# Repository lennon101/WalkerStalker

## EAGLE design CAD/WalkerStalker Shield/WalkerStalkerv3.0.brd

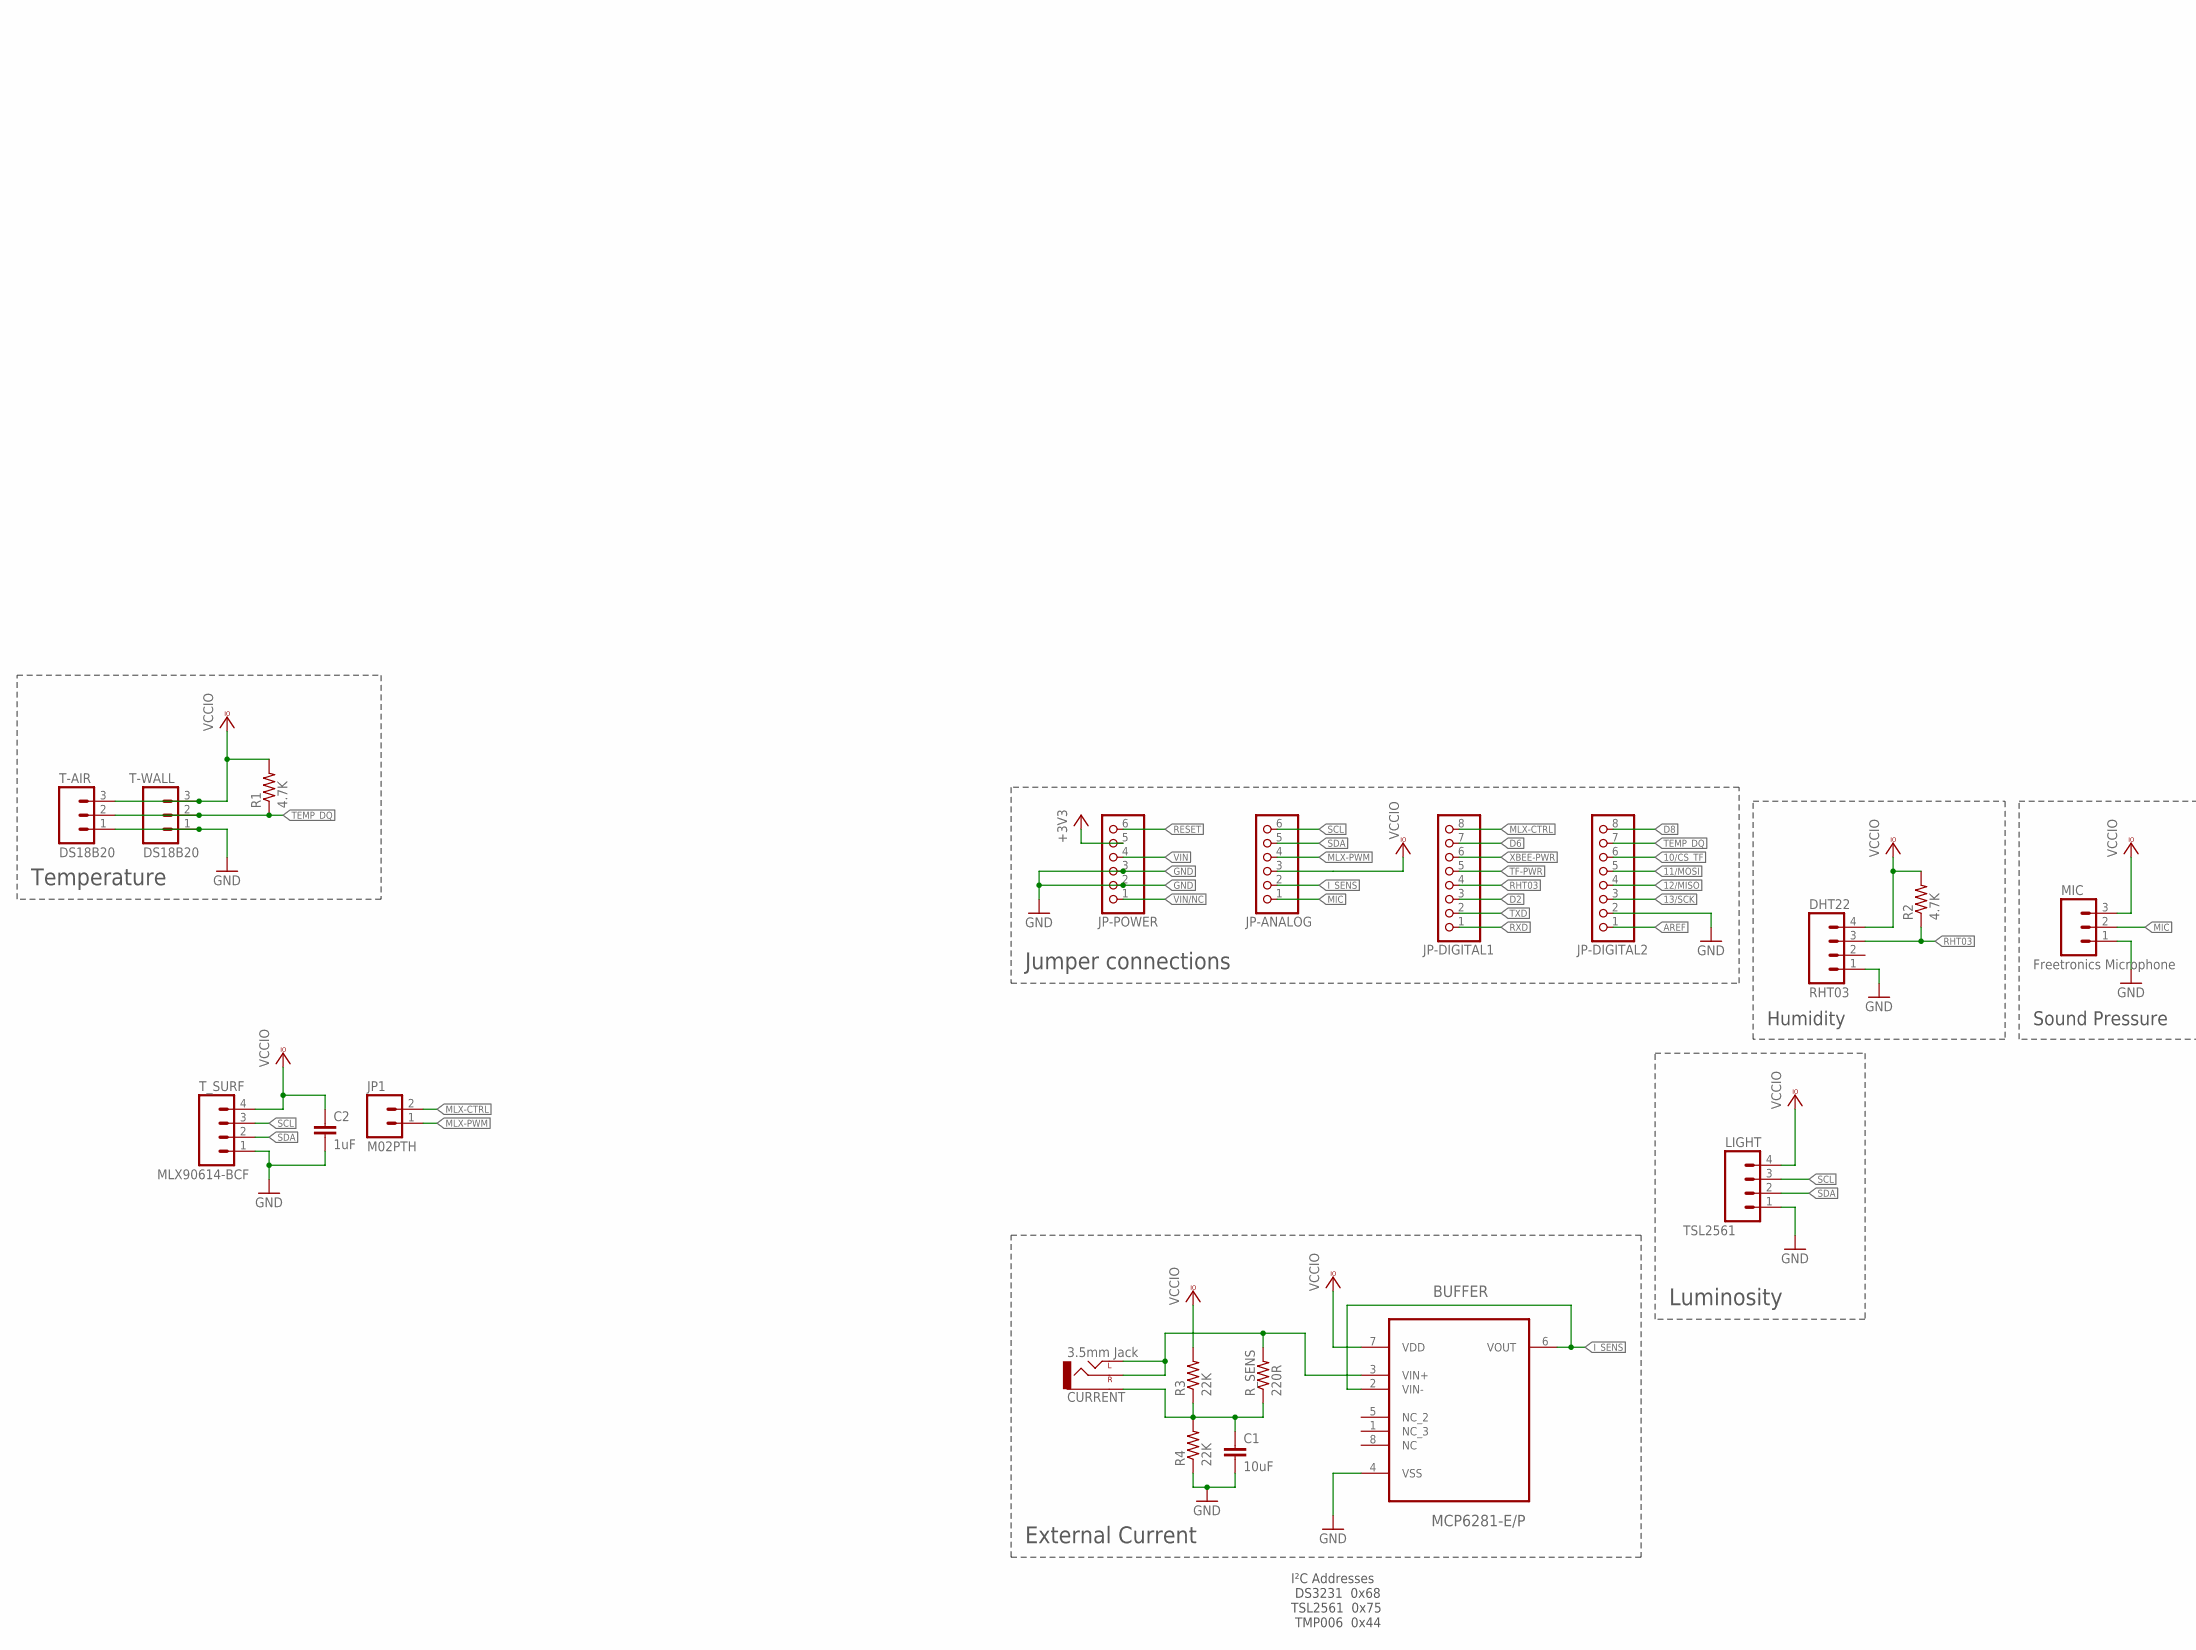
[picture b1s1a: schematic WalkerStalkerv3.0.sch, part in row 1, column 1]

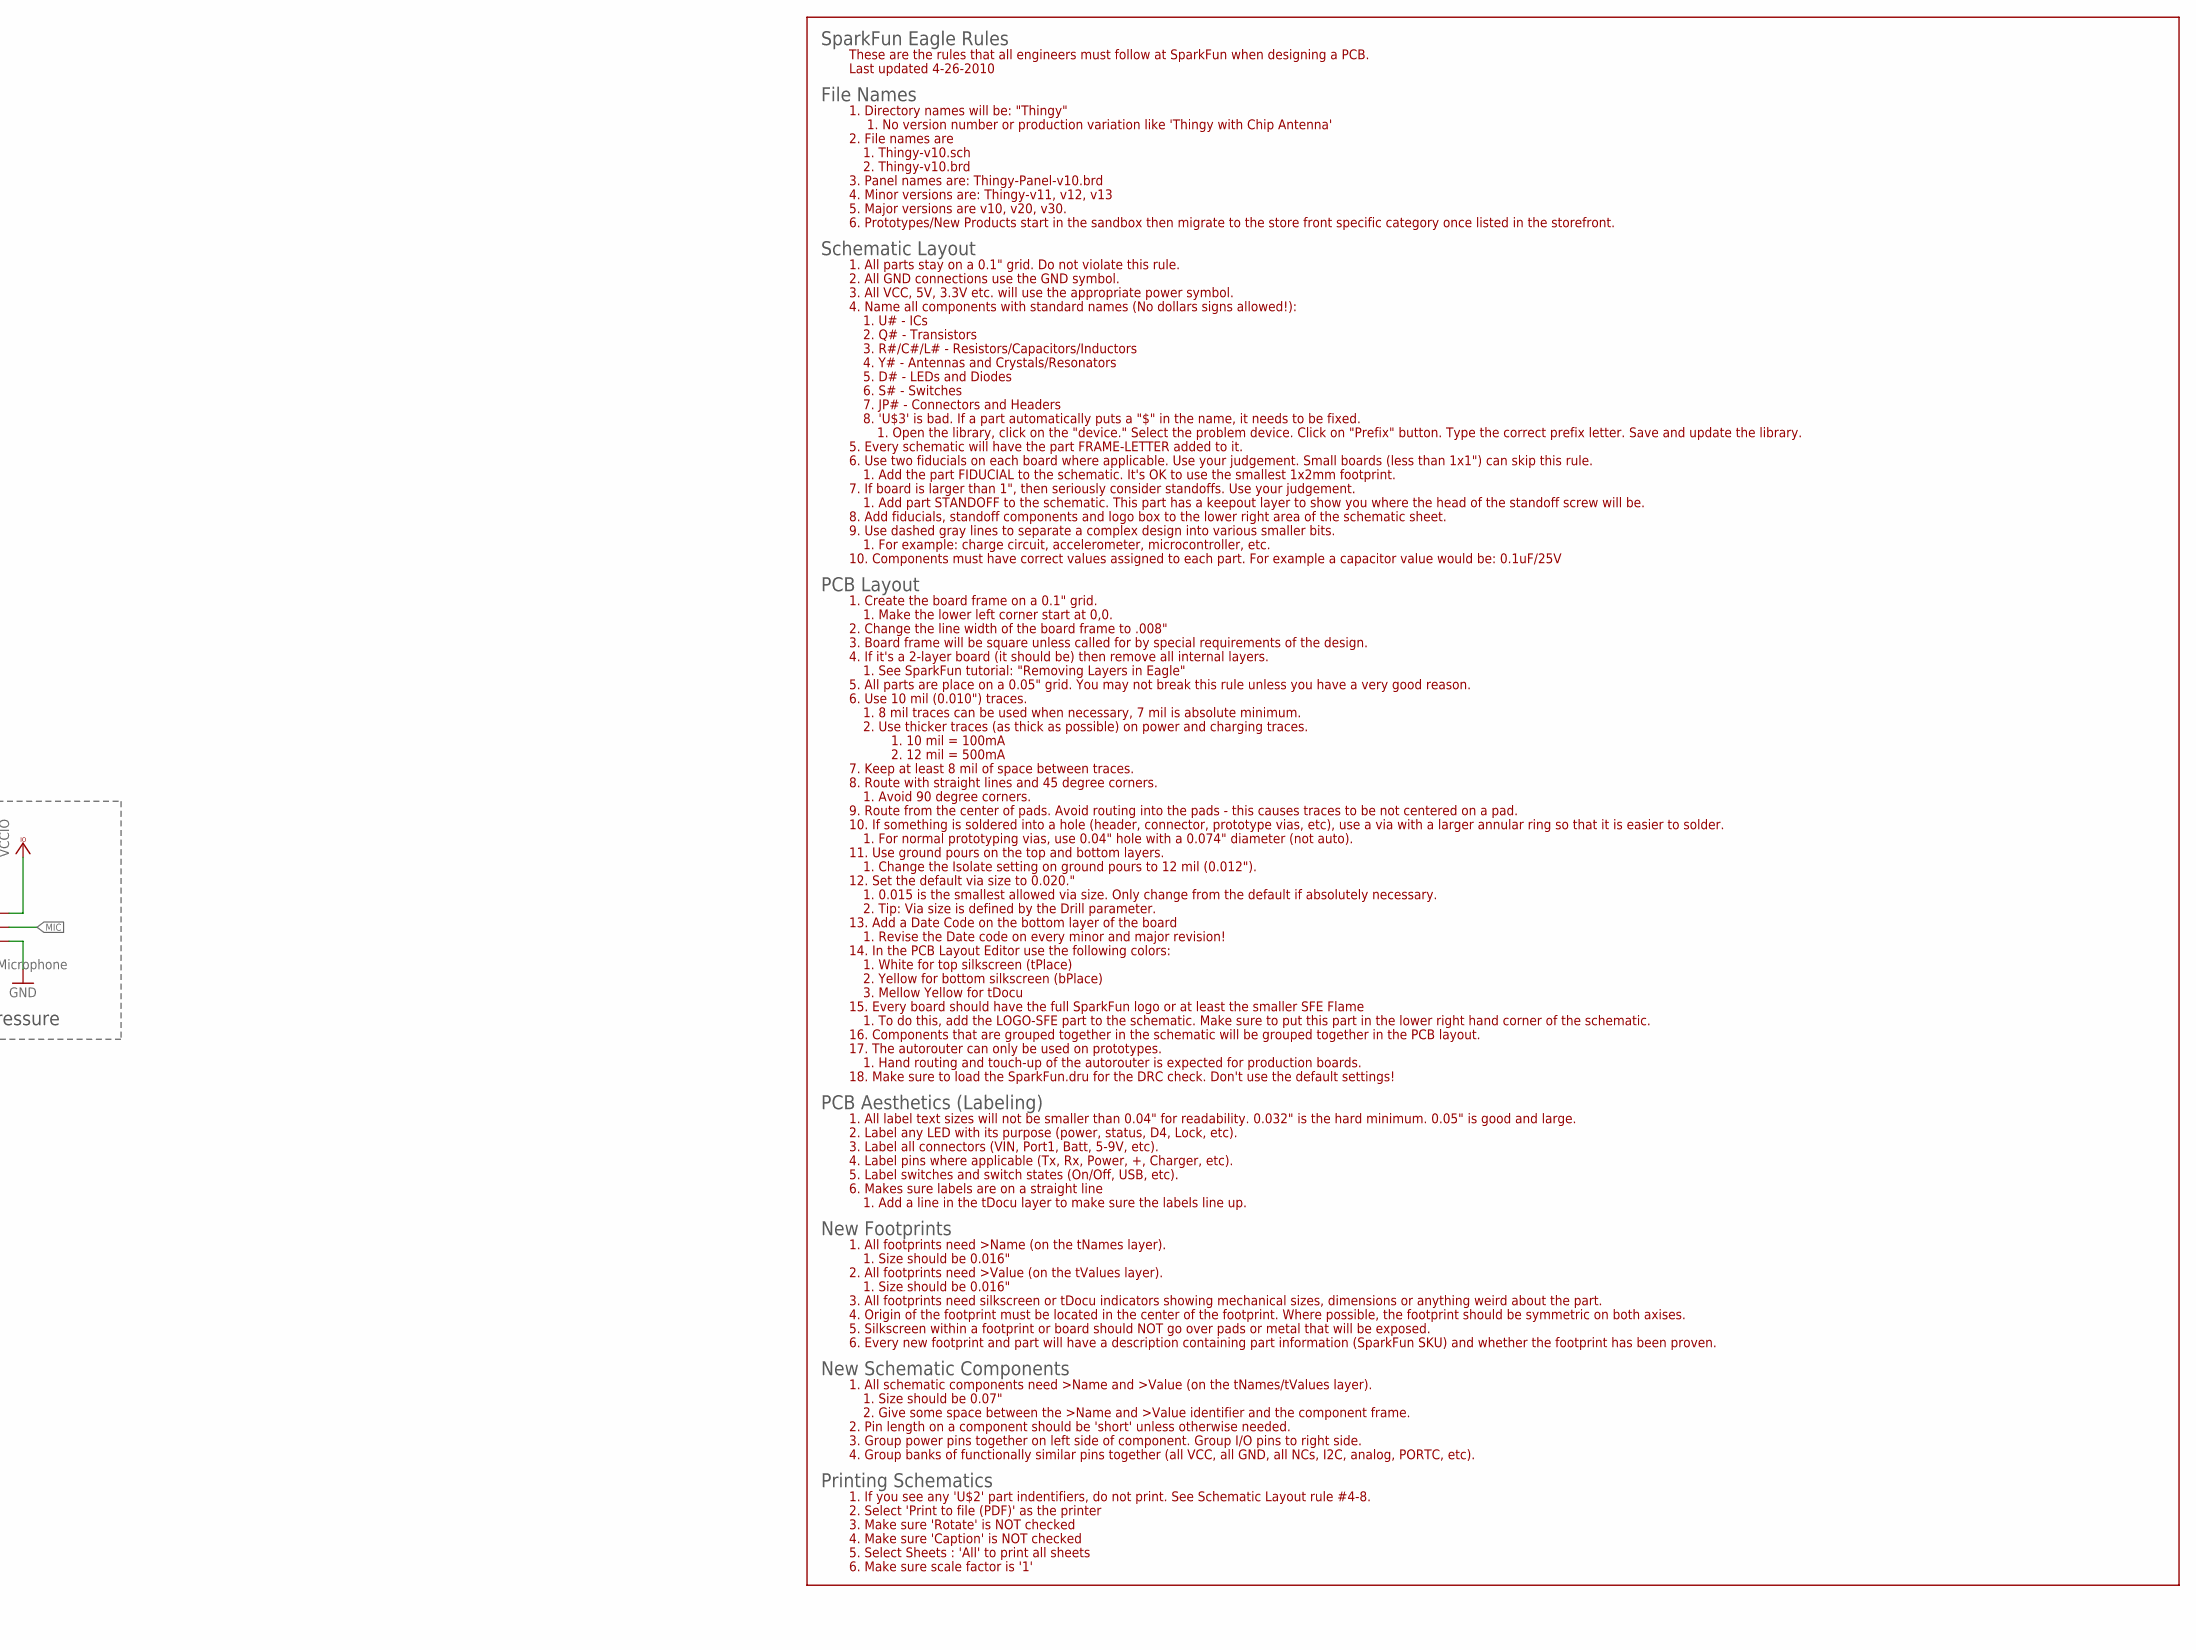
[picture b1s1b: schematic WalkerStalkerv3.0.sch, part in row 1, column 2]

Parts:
BUFFER: MCP6281-E/P; DIP254P762X432-8
C1: 10uF; 1206
C2: 1uF; 1206
CURRENT: 3.5mm Jack; AUDIO-JACK
DHT22: RHT03; 1X04
JP1: M02PTH; 1X02
JP-ANALOG: PINHD-1X6CB; 1X06-CLEANBIG
JP-DIGITAL1, JP-DIGITAL2: PINHD-1X8CLEANBIG; 1X08-CLEANBIG
JP-POWER: PINHD-1X6CB; 1X06-CLEANBIG
LIGHT: TSL2561; 1X04
MIC: Freetronics Microphone; 1X03
R1, R2: 4.7K; 1206
R3, R4: 22K; 1206
R_SENS: 220R; 1206
T-AIR: DS18B20; 1X03
T-WALL: DS18B20; 1X03
T_SURF: MLX90614-BCF; 1X04

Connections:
10/CS_TF: JP-DIGITAL2.6
11/MOSI: JP-DIGITAL2.5
12/MISO: JP-DIGITAL2.4
13/SCK: JP-DIGITAL2.3
+3V3: JP-POWER.5
AREF: JP-DIGITAL2.1
D2: JP-DIGITAL1.3
D6: JP-DIGITAL1.7
D8: JP-DIGITAL2.8
GND: BUFFER.4 (VSS), C1.2, C2.2, DHT22.1, JP-DIGITAL2.2, JP-POWER.2, JP-POWER.3, LIGHT.1, MIC.1, R4.1, T-AIR.1, T-WALL.1, T_SURF.1
I_SENS: BUFFER.2 (VIN-), BUFFER.6 (VOUT), JP-ANALOG.2
MIC: JP-ANALOG.1, MIC.2
MLX-CTRL: JP1.2, JP-DIGITAL1.8
MLX-PWM: JP1.1, JP-ANALOG.4
unnamed: BUFFER.3 (VIN+), CURRENT.RING (RIGHT), CURRENT.TIP (LEFT), R_SENS.2
unnamed: C1.1, CURRENT.SLEEVE, R3.1, R4.2, R_SENS.1
RESET: JP-POWER.6
RHT03: DHT22.3, JP-DIGITAL1.4, R2.1
RXD: JP-DIGITAL1.1
SCL: JP-ANALOG.6, LIGHT.3, T_SURF.3
SDA: JP-ANALOG.5, LIGHT.2, T_SURF.2
TEMP_DQ: JP-DIGITAL2.7, R1.1, T-AIR.2, T-WALL.2
TF-PWR: JP-DIGITAL1.5
TXD: JP-DIGITAL1.2
VCCIO: BUFFER.7 (VDD), C2.1, DHT22.4, JP-ANALOG.3, LIGHT.4, MIC.3, R1.2, R2.2, R3.2, T-AIR.3, T-WALL.3, T_SURF.4
VIN: JP-POWER.4
VIN/NC: JP-POWER.1
XBEE-PWR: JP-DIGITAL1.6

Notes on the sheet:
Jumper connections
External Current
Temperature
Humidity
Luminosity
Sound Pressure
I²C Addresses DS3231 0x68 TSL2561 0x75 TMP006 0x44

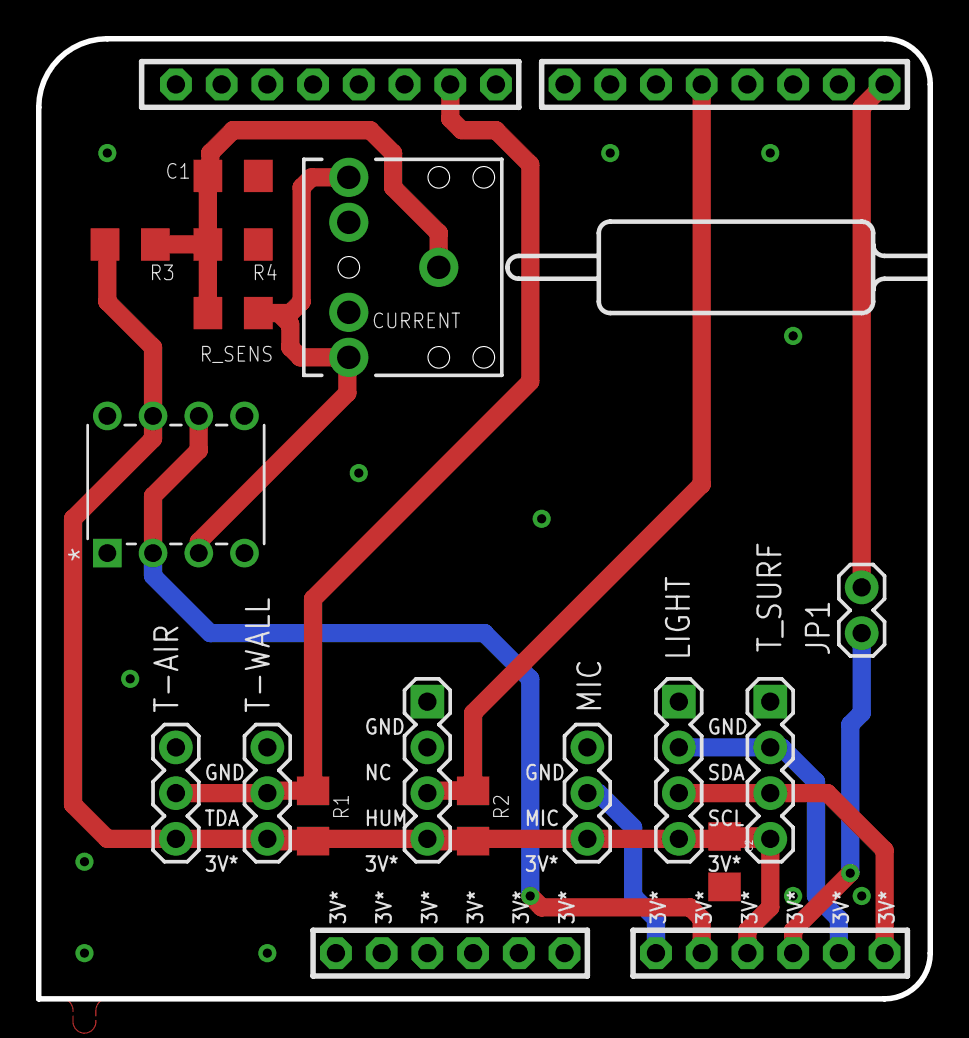
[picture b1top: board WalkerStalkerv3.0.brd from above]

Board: 2 copper layers, 49.5 x 53.3 mm, 20 parts (0 on the bottom side), 12 nets.

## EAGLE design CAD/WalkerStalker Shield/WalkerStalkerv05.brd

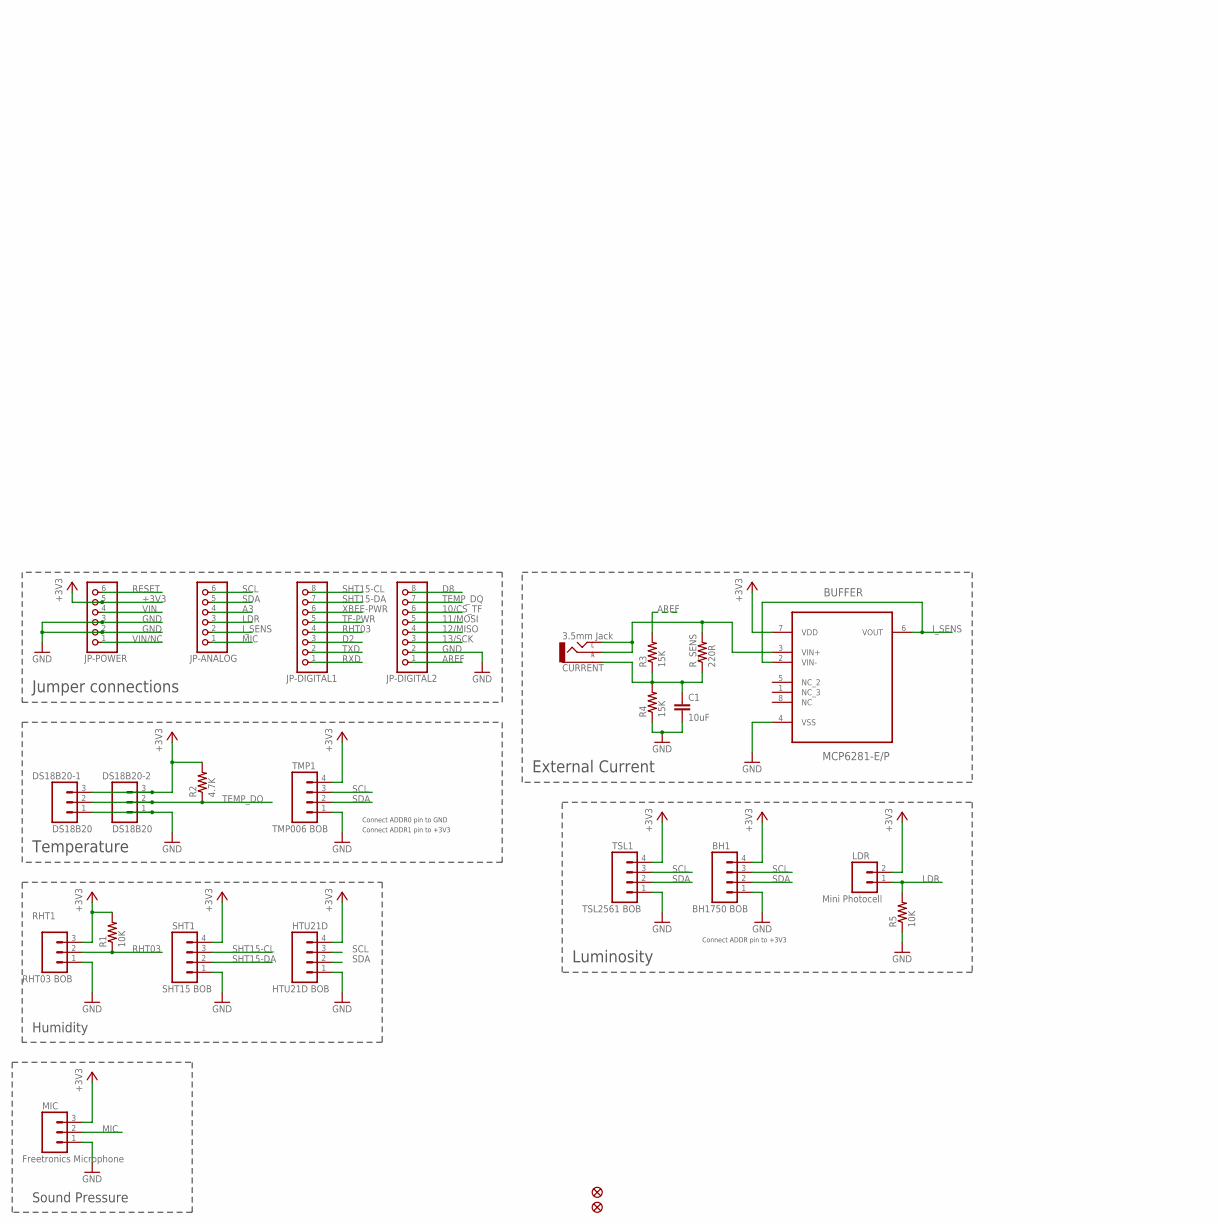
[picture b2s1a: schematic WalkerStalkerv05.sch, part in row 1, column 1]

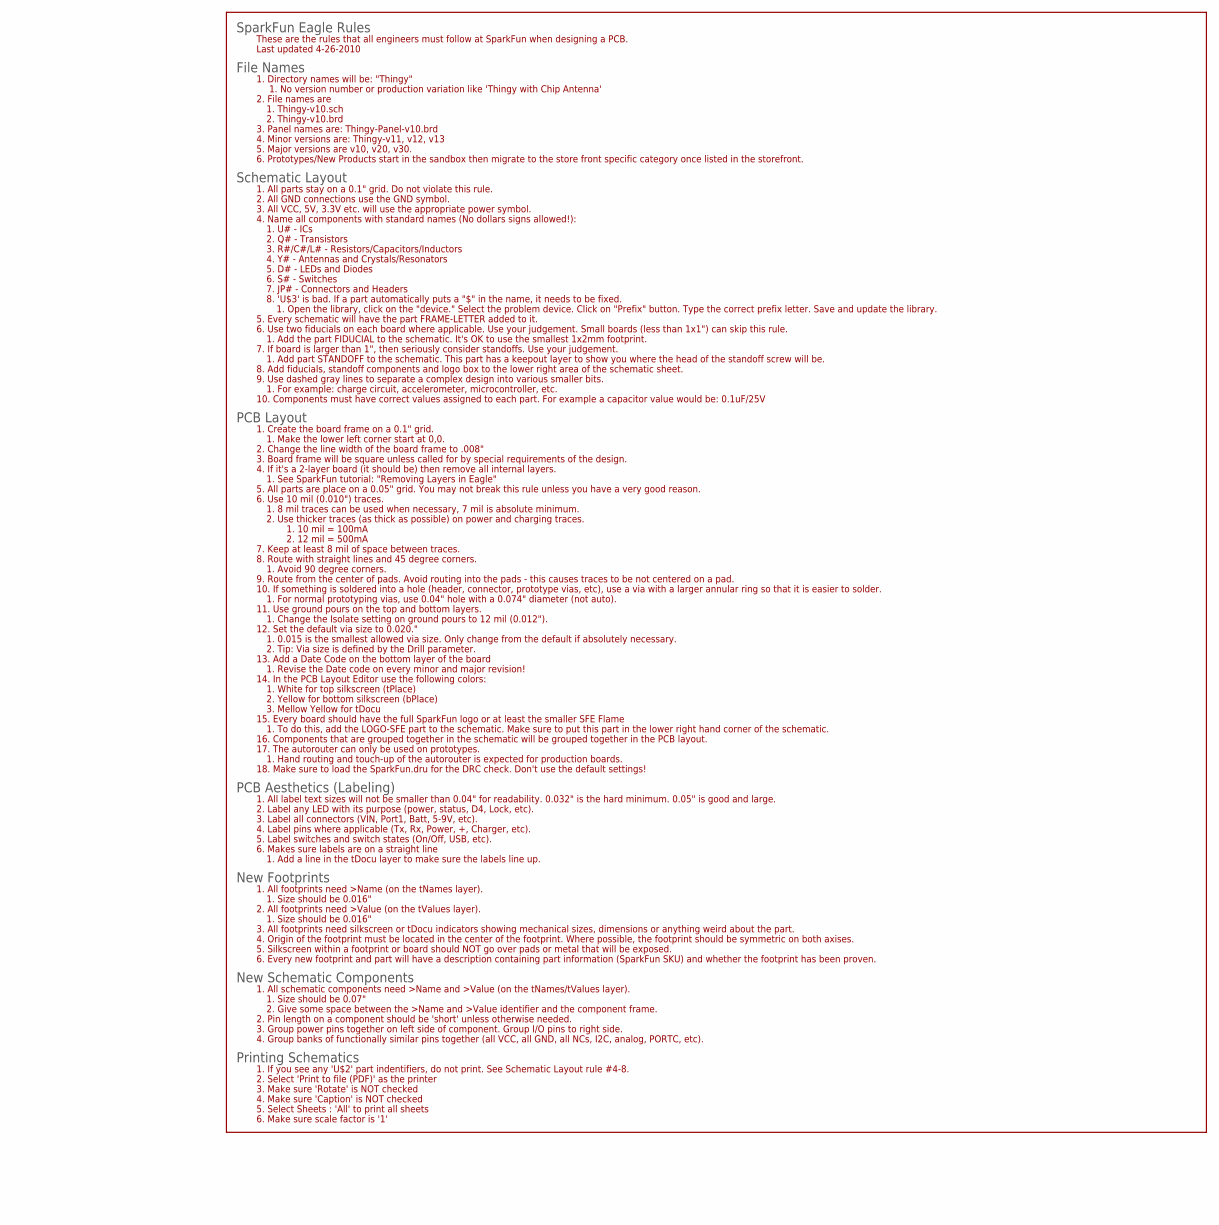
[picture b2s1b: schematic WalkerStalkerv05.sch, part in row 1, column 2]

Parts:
BH1: BH1750 BOB; MOLEX-1X4
BUFFER: MCP6281-E/P; DIP254P762X432-8
C1: 10uF; 1206
CURRENT: 3.5mm Jack; AUDIO-JACK
DS18B20-1, DS18B20-2: DS18B20; MOLEX-1X3
FID1, FID2: FIDUCIAL1.5X3; FIDUCIAL-1.5X3
HTU21D: HTU21D BOB; MOLEX-1X4
JP-ANALOG: PINHD-1X6CB; 1X06-CLEANBIG
JP-DIGITAL1, JP-DIGITAL2: PINHD-1X8CLEANBIG; 1X08-CLEANBIG
JP-POWER: PINHD-1X6CB; 1X06-CLEANBIG
LDR: Mini Photocell; MOLEX-1X2
MIC: Freetronics Microphone; MOLEX-1X3
R1, R5: 10K; 1206
R2: 4.7K; 1206
R3, R4: 15K; 1206
RHT1: RHT03 BOB; MOLEX-1X3
R_SENS: 220R; 1206
SHT1: SHT15 BOB; MOLEX-1X4
TMP1: TMP006 BOB; MOLEX-1X4
TSL1: TSL2561 BOB; MOLEX-1X4

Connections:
10/CS_TF: JP-DIGITAL2.6
11/MOSI: JP-DIGITAL2.5
12/MISO: JP-DIGITAL2.4
13/SCK: JP-DIGITAL2.3
+3V3: BH1.4, BUFFER.7 (VDD), DS18B20-1.3, DS18B20-2.3, HTU21D.4, JP-POWER.5, LDR.2, MIC.3, R1.2, R2.2, RHT1.3, SHT1.4, TMP1.4, TSL1.4
A3: JP-ANALOG.4
AREF: JP-DIGITAL2.1, R3.2
D2: JP-DIGITAL1.3
D8: JP-DIGITAL2.8
GND: BH1.1, BUFFER.4 (VSS), C1.2, DS18B20-1.1, DS18B20-2.1, HTU21D.1, JP-DIGITAL2.2, JP-POWER.2, JP-POWER.3, MIC.1, R4.1, R5.1, RHT1.1, SHT1.1, TMP1.1, TSL1.1
I_SENS: BUFFER.2 (VIN-), BUFFER.6 (VOUT), JP-ANALOG.2
LDR: JP-ANALOG.3, LDR.1, R5.2
MIC: JP-ANALOG.1, MIC.2
unnamed: BUFFER.3 (VIN+), CURRENT.RING (RIGHT), CURRENT.TIP (LEFT), R_SENS.2
unnamed: C1.1, CURRENT.SLEEVE, R3.1, R4.2, R_SENS.1
RESET: JP-POWER.6
RHT03: JP-DIGITAL1.4, R1.1, RHT1.2
RXD: JP-DIGITAL1.1
SCL: BH1.3, HTU21D.3, JP-ANALOG.6, TMP1.3, TSL1.3
SDA: BH1.2, HTU21D.2, JP-ANALOG.5, TMP1.2, TSL1.2
SHT15-CL: JP-DIGITAL1.8, SHT1.3
SHT15-DA: JP-DIGITAL1.7, SHT1.2
TEMP_DQ: DS18B20-1.2, DS18B20-2.2, JP-DIGITAL2.7, R2.1
TF-PWR: JP-DIGITAL1.5
TXD: JP-DIGITAL1.2
VIN: JP-POWER.4
VIN/NC: JP-POWER.1
XBEE-PWR: JP-DIGITAL1.6

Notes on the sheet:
Jumper connections
External Current
Temperature
Humidity
Luminosity
Sound Pressure
Connect ADDR pin to +3V3
Connect ADDR0 pin to GND
Connect ADDR1 pin to +3V3

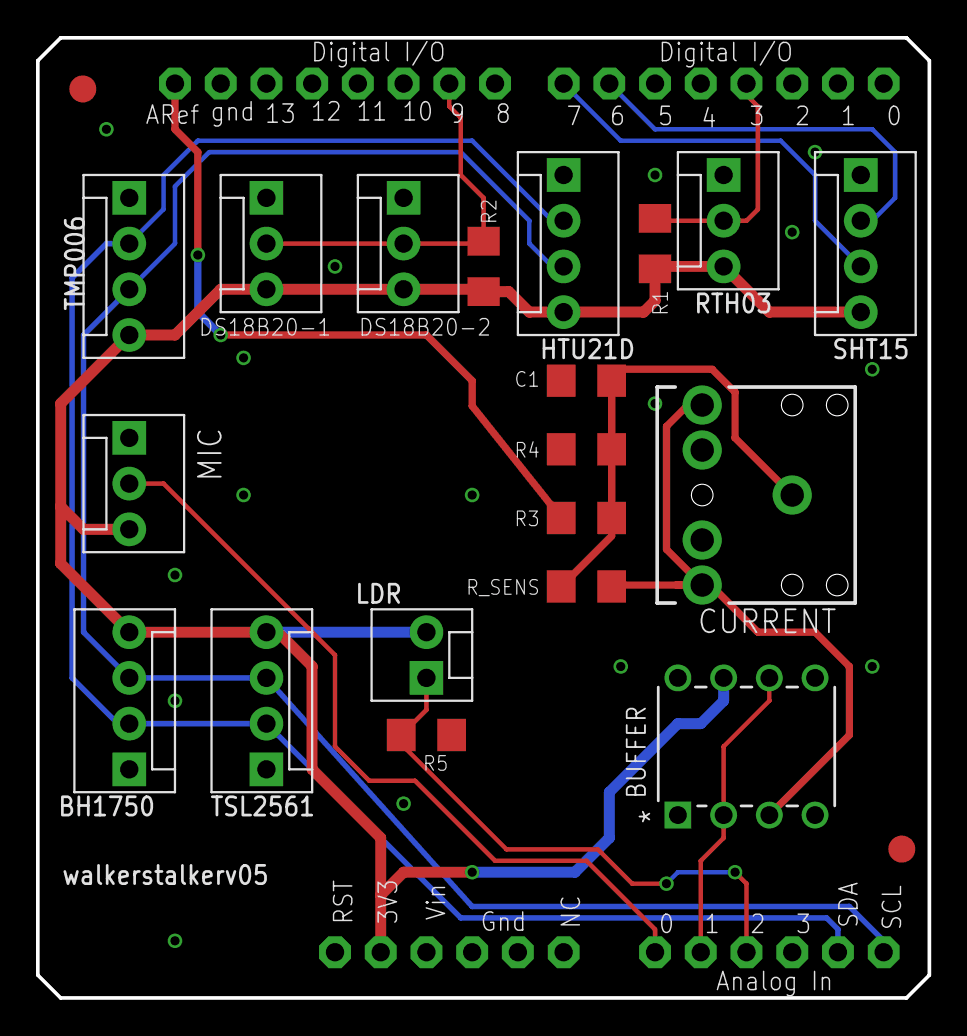
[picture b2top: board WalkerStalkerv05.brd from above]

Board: 2 copper layers, 49.5 x 53.3 mm, 25 parts (0 on the bottom side), 14 nets.

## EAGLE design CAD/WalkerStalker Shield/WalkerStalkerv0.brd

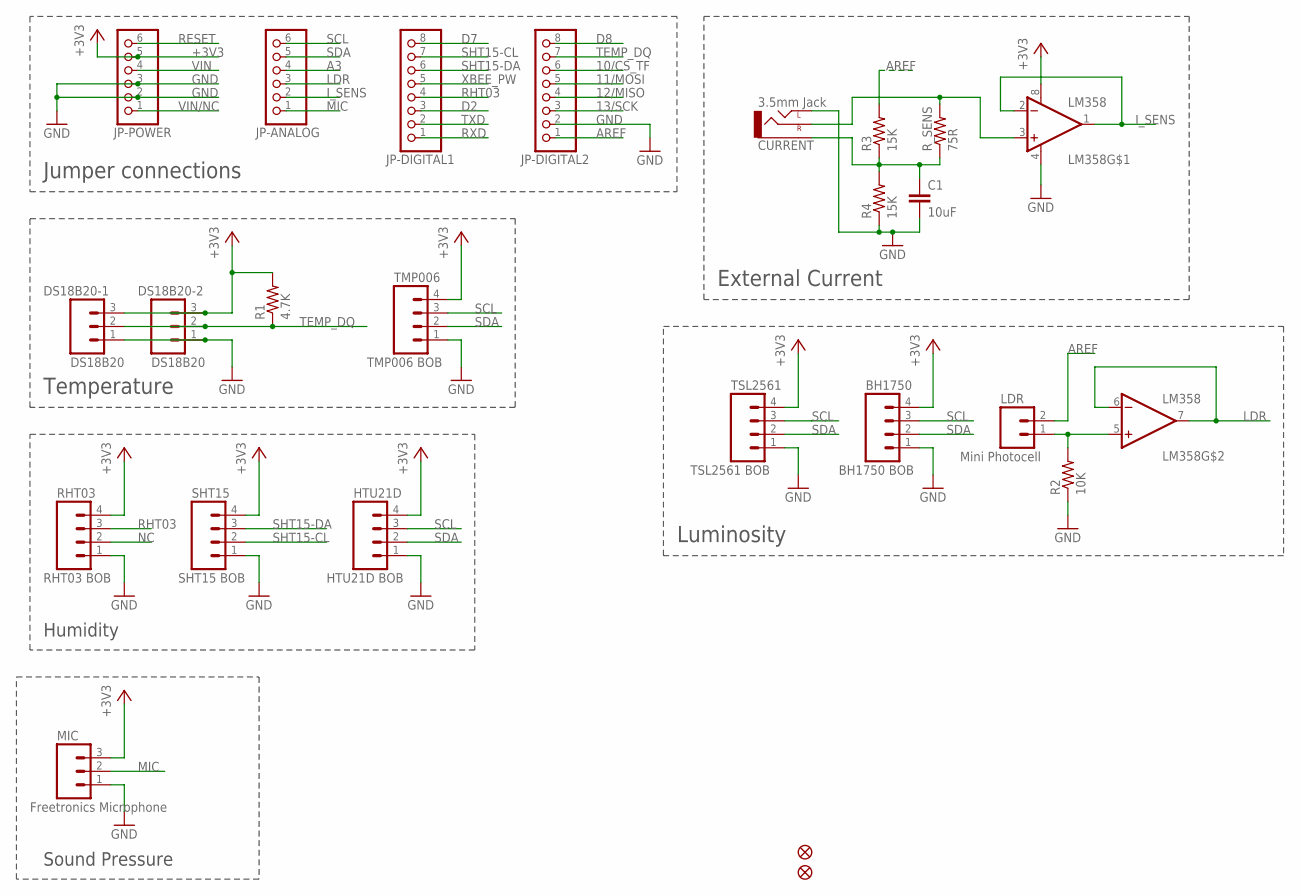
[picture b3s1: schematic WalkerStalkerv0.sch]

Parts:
BH1750: BH1750 BOB; MOLEX-1X4
C1: 10uF; 1206
CURRENT: 3.5mm Jack; AUDIO-JACK
DS18B20-1, DS18B20-2: DS18B20; MOLEX-1X3
FID1, FID2: FIDUCIAL1.5X3; FIDUCIAL-1.5X3
HTU21D: HTU21D BOB; MOLEX-1X4
JP-ANALOG: PINHD-1X6CB; 1X06-CLEANBIG
JP-DIGITAL1, JP-DIGITAL2: PINHD-1X8CLEANBIG; 1X08-CLEANBIG
JP-POWER: PINHD-1X6CB; 1X06-CLEANBIG
LDR: Mini Photocell; MOLEX-1X2
LM358: LM358; DIP08
MIC: Freetronics Microphone; MOLEX-1X3
R1: 4.7K; 1206
R2: 10K; 1206
R3, R4: 15K; 1206
RHT03: RHT03 BOB; MOLEX-1X4
R_SENS: 75R; 1206
SHT15: SHT15 BOB; MOLEX-1X4
TMP006: TMP006 BOB; MOLEX-1X4
TSL2561: TSL2561 BOB; MOLEX-1X4

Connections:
10/CS_TF: JP-DIGITAL2.6
11/MOSI: JP-DIGITAL2.5
12/MISO: JP-DIGITAL2.4
13/SCK: JP-DIGITAL2.3
+3V3: BH1750.4, DS18B20-1.3, DS18B20-2.3, HTU21D.4, JP-POWER.5, LM358.8 (V+), MIC.3, R1.2, RHT03.4, SHT15.4, TMP006.4, TSL2561.4
A3: JP-ANALOG.4
AREF: JP-DIGITAL2.1, LDR.2, R3.2
D2: JP-DIGITAL1.3
D7: JP-DIGITAL1.8
D8: JP-DIGITAL2.8
GND: BH1750.1, C1.2, CURRENT.TIP (LEFT), DS18B20-1.1, DS18B20-2.1, HTU21D.1, JP-DIGITAL2.2, JP-POWER.2, JP-POWER.3, LM358.4 (V-), MIC.1, R2.1, R4.1, RHT03.1, SHT15.1, TMP006.1, TSL2561.1
I_SENS: JP-ANALOG.2, LM358.1 (OUT), LM358.2 (-IN)
LDR: JP-ANALOG.3, LM358.6 (-IN), LM358.7 (OUT)
LDR_OUT: LDR.1, LM358.5 (+IN), R2.2
MIC: JP-ANALOG.1, MIC.2
N$: CURRENT.RING (RIGHT), LM358.3 (+IN), R_SENS.2
unnamed: C1.1, CURRENT.SLEEVE, R3.1, R4.2, R_SENS.1
NC: RHT03.2
RESET: JP-POWER.6
RHT03: JP-DIGITAL1.4, RHT03.3
RXD: JP-DIGITAL1.1
SCL: BH1750.3, HTU21D.3, JP-ANALOG.6, TMP006.3, TSL2561.3
SDA: BH1750.2, HTU21D.2, JP-ANALOG.5, TMP006.2, TSL2561.2
SHT15-CL: JP-DIGITAL1.7, SHT15.2
SHT15-DA: JP-DIGITAL1.6, SHT15.3
TEMP_DQ: DS18B20-1.2, DS18B20-2.2, JP-DIGITAL2.7, R1.1
TXD: JP-DIGITAL1.2
VIN: JP-POWER.4
VIN/NC: JP-POWER.1
XBEE_PW: JP-DIGITAL1.5

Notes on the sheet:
Jumper connections
External Current
Temperature
Humidity
Luminosity
Sound Pressure

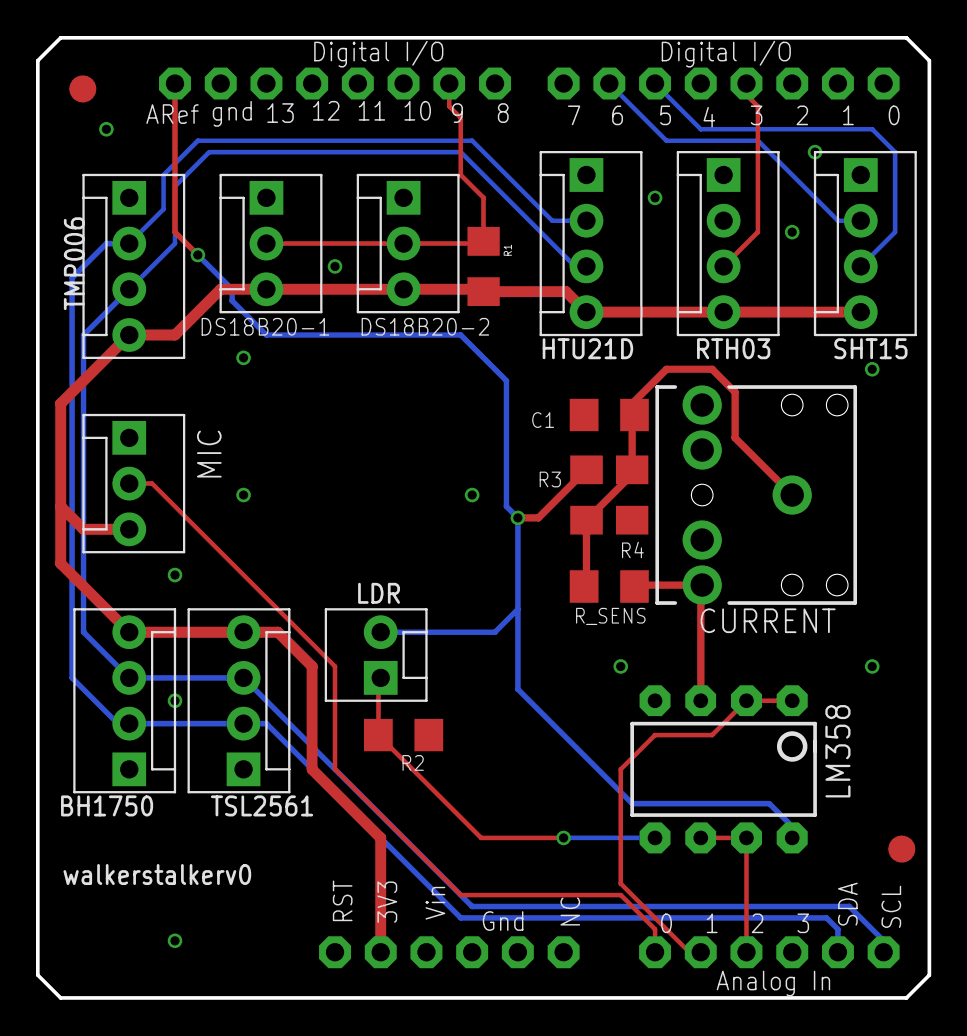
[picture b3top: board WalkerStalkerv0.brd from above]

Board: 2 copper layers, 49.5 x 53.3 mm, 24 parts (0 on the bottom side), 15 nets.

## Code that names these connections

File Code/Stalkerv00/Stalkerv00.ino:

#include <XBee.h>
#include <Adafruit_Sensor.h>
#include <pgmspace.h>
#include <Adafruit_TSL2561_U.h>
#include <SHT15.h>
#include <HTU21D.h>
#include "Arduino.h"
#include <DS3231.h>
#include <DHT.h>
#include <Wire.h>
#include <Adafruit_TMP006.h>
#include <OneWire.h>
#include <DallasTemperature.h>

const char FILENAME[] = "DATALOG.txt";
uint8_t payload[48];

XBee xbee = XBee();

XBeeAddress64 addr64 = XBeeAddress64(0x0013a200, 0x403e0f30);
ZBTxRequest zbTx = ZBTxRequest(addr64, payload, sizeof(payload));
ZBTxStatusResponse txStatus = ZBTxStatusResponse();

#define AIR_TEMP_PIN 9
OneWire oneWire(AIR_TEMP_PIN);
DallasTemperature airTempSensors(&oneWire);
Adafruit_TMP006 surfaceTempSensor;

#define RHT03_PIN 3
#define RHT03_TYPE DHT22
#define RHT03_COUNT 3
DHT humiditySensor03(RHT03_PIN, RHT03_TYPE, RHT03_COUNT);

#define SHT15_CLK_PIN 6
#define SHT15_DATA_PIN 5
SHT15 humiditySensor15(SHT15_CLK_PIN, SHT15_DATA_PIN);

#define LDR_PIN 2
Adafruit_TSL2561_Unified lightSensor = Adafruit_TSL2561_Unified(TSL2561_ADDR_FLOAT);

#define MIC_PIN 0
#define MIC_SAMPLE_PERIOD 100

DS3231 RTC;

#define CHIP_SELECT_PIN 10

HTU21D humiditySensor21;

void setup()
{
	// Comms
	Serial.begin(57600);
	Wire.begin();
	
	Serial.println("Awake");
	
	RTC.begin();
	
	airTempSensors.begin();
	surfaceTempSensor.begin(TMP006_CFG_1SAMPLE);

	humiditySensor03.begin();
	humiditySensor21.begin();

	lightSensor.begin();
}

void loop()
{
	// Request Values
	airTempSensors.requestTemperatures();

	// Read values
	float airTemp1 = airTempSensors.getTempCByIndex(0);
	float airTemp2 = airTempSensors.getTempCByIndex(1);
	
	float surfaceTemp = surfaceTempSensor.readObjTempC();
	
	float temp03 = humiditySensor03.readTemperature();
	float humidity03 = humiditySensor03.readHumidity();
	
	float temp21 = humiditySensor21.readTemperature();
	float humidity21 = humiditySensor21.readHumidity();
	humidity21 = getCorrectHTU21DHumidity(temp21, humidity21);
	
	float temp15 = humiditySensor15.readTemperature();
	float humidity15 = humiditySensor15.readHumidity();
	
	sensors_event_t event;
	lightSensor.getEvent(&event);
	int lightLevel = event.light;
	int ldrLightLevel = analogRead(LDR_PIN);
	
	int soundLevel = getSoundLevel(MIC_SAMPLE_PERIOD);
	
	// Print values
	DateTime timeStamp = RTC.now();
	printTimeStamp(timeStamp);
	
	Serial.println("\n--- Temperature");
	Serial.print("DS18B20 1 (C): ");
	Serial.println(airTemp1, 2);
	
	Serial.print("DS18B20 2 (C): ");
	Serial.println(airTemp2);
	
	Serial.print("TMP006 - Surface (C): ");
	Serial.println(surfaceTemp);
	
	Serial.print("RHT03 (C): ");
	Serial.println(temp03, 2);
	
	Serial.print("HTU21D (C): ");
	Serial.println(temp21, 2);
	
	Serial.print("SHT15 (C): ");
	Serial.println(temp15, 2);
	
	Serial.println("\n--- Humidity");
	
	Serial.print("RHT03 (%): ");
	Serial.println(humidity03, 2);
	
	Serial.print("HTU21D (%): ");
	Serial.println(humidity21, 2);
	
	Serial.print("SHT15 (%): ");
	Serial.println(humidity15, 2);
	
	Serial.println("\n--- Illuminance");
	
	Serial.print("TSL2561 (lux): ");
	Serial.println(lightLevel);
	
	Serial.print("LDR (counts): ");
	Serial.println(ldrLightLevel);
	
	Serial.println("\n--- Sound Pressure");
	
	Serial.print("Mic (counts): ");
	Serial.println(soundLevel);
	
	Serial.println("----------------------------------");


	// Write to SD card
	delay(1000);
}




/**
* Print the current time in hh:mm:ss
*/
void printTimeStamp(DateTime timeStamp){
	
	Serial.print("\n-- ");
	Serial.print(timeStamp.hour(), DEC);
	Serial.print(":");
	Serial.print(timeStamp.minute(), DEC);
	Serial.print(":");
	Serial.print(timeStamp.second(), DEC);
	Serial.println(" --");
}


/**
* Get the corrected relative humidity after apply conversion coefficients
*
* @param temperature The temperature of the HTU21D sensor in °C
* @param humidity The relative humidity reading of the HTU21D sensor in %
* @return The corrected humidity value in %
*/
float getCorrectHTU21DHumidity(float temperature, float humidity){
	float correctedHumidity = humidity + (25 - temperature)*-0.15;
	return correctedHumidity;
}


/**
* Get the maximum sound level over the specified sampling period
*
* @param samplePeriod Listening period for the sampling in ms.
* @return Maximum sound level in 10-bit counts
*/
int getSoundLevel(int samplePeriod){
	unsigned long startTime = millis();
	int maxSoundLevel = 0;
	
	while (millis() < (startTime + samplePeriod) && samplePeriod > 0){
		int soundLevel = analogRead(MIC_PIN);
		
		if (soundLevel > maxSoundLevel){
			maxSoundLevel = soundLevel;
		}
	}
	
	return maxSoundLevel;
}

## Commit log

2014-04-11 Repo Started
2014-04-15 Improved serial output
    - Removed old and redundant code
    - Printed/Transmitted sensor data is easier to read at the expense of a
    few extra bytes in each packet
    - Sound level output is now an average rather than maximum, as averages
    give more accurate conversions
    - Printing the time now pads a zero to the seconds if needed
2014-04-16 HTU21D Library fixed
2014-04-26 Prototype Update
    - Prototype deployment code added (Stalkerv02)
    - Production code cloned in preparation for the next version of the
    sensor module
    - WalkerStalker code greatly optimised since last update
2014-05-07 v20 Update
    - Removed some sensors (SHT15, RHT03, LDR, BH1750FVI)
    - Transmission now occurs in packets for reduced redundancy
    - Current consumption & sound are now active again
    - XBee transmission is now in API mode, and in packets
2014-05-12 Minor Changes
    Can't remember doing anything
2014-07-14 Fixed Temperature sensors
    + Temperature sensors are now called by explicit address, rather than
    index, which was not consistent (could not tell if sensor was wall or
    air)
    + Unit IDs are not transmitted in data packets for easy identification
    +Mounting bracket for TMP006 sensor added (3D file)
2014-07-30 New folder structure
    + Changed the sample delay window to 20s
2014-08-14 Added debug output to v20 code
    + Changed the address of the coordinator to the default address to let
    the network sort itself out
    - Removed a lot of useless receive code from the xbee transmit function
2014-11-05 Attempted auto-retry for XBee transmission
2015-01-15 Checkpoint - Before separation of config file
    - I'm fairy certain no functional changes have been made.
    - I should really gitignore the build files...
2015-01-15 Updated GitIgnore
2015-01-15 Updated GitAttributes
2015-01-27 Removing ignored files. Brace for impact
2015-02-09 Walker v3 Firmware
    + Changed DHT22 library - much more reliable
2015-04-30 Not sure
2015-05-01 Moving folders around for clarity
2015-05-01 Cleaning up folders
2015-05-01 More cleaning
2015-07-04 add comments to WalkerStalker.ino
2015-07-04 add comments to code again
2015-07-04 add Project-Files-v3 folder

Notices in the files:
parts and their libraries:
SparkFun-Connectors: Licensing: CC v3.0 Share-Alike You are welcome to use this library for commercial purposes.
